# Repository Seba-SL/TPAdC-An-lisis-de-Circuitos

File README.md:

<h1>  TP - Análisis-de-Circuitos </h1>

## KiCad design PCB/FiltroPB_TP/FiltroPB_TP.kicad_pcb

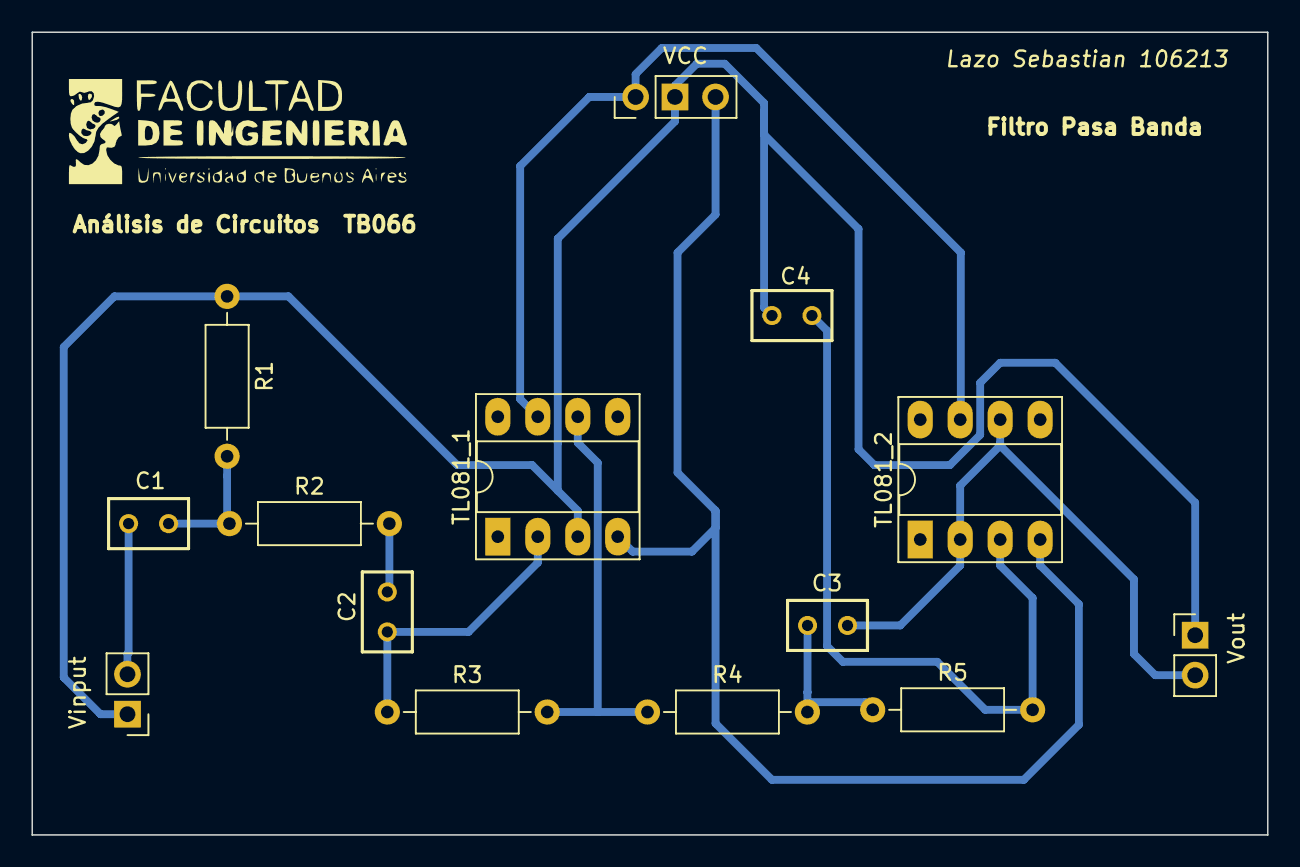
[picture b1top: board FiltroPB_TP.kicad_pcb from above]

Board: 2 copper layers, 78.5 x 51.0 mm, 14 parts (0 on the bottom side), 11 nets.

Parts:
C1, C2, C3: 1u; C320C
C4: 2.2n; C320C
R1, R2, R3: 10k; R_Axial_DIN0207_L6.3mm_D2.5mm_P10.16mm_Horizontal
R4: 1.25k; R_Axial_DIN0207_L6.3mm_D2.5mm_P10.16mm_Horizontal
R5: 100k; R_Axial_DIN0207_L6.3mm_D2.5mm_P10.16mm_Horizontal
TL081_1, TL081_2: TL081; DIP-8_W7.62mm_Socket_LongPads
VCC: Alimentación +/- 15 V; PinHeader_1x03_P2.54mm_Vertical
Vinput: Entrada de Señal; PinHeader_1x02_P2.54mm_Vertical
Vout: Salida de Señal; PinHeader_1x02_P2.54mm_Vertical

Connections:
0: C4.2, R1.1, TL081_1.3 (+), VCC.1, Vinput.1, Vout.1
unnamed: C1.1, R1.2, R2.1
unnamed: C2.2, R2.2
unnamed: C3.1, R4.2, R5.1
unnamed: R3.2, R4.1, TL081_1.6
unnamed: C2.1, R3.1, TL081_1.2 (-)
unnamed: C4.1, R5.2, TL081_2.3 (+)
Vcc+: TL081_1.7 (V+), TL081_2.7 (V+), VCC.2
Vcc-: TL081_1.4 (V-), TL081_2.4 (V-), VCC.3
Vinput: C1.2, Vinput.2
Vout: C3.2, TL081_2.2 (-), TL081_2.6, Vout.2

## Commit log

2025-02-23 Ltspice
